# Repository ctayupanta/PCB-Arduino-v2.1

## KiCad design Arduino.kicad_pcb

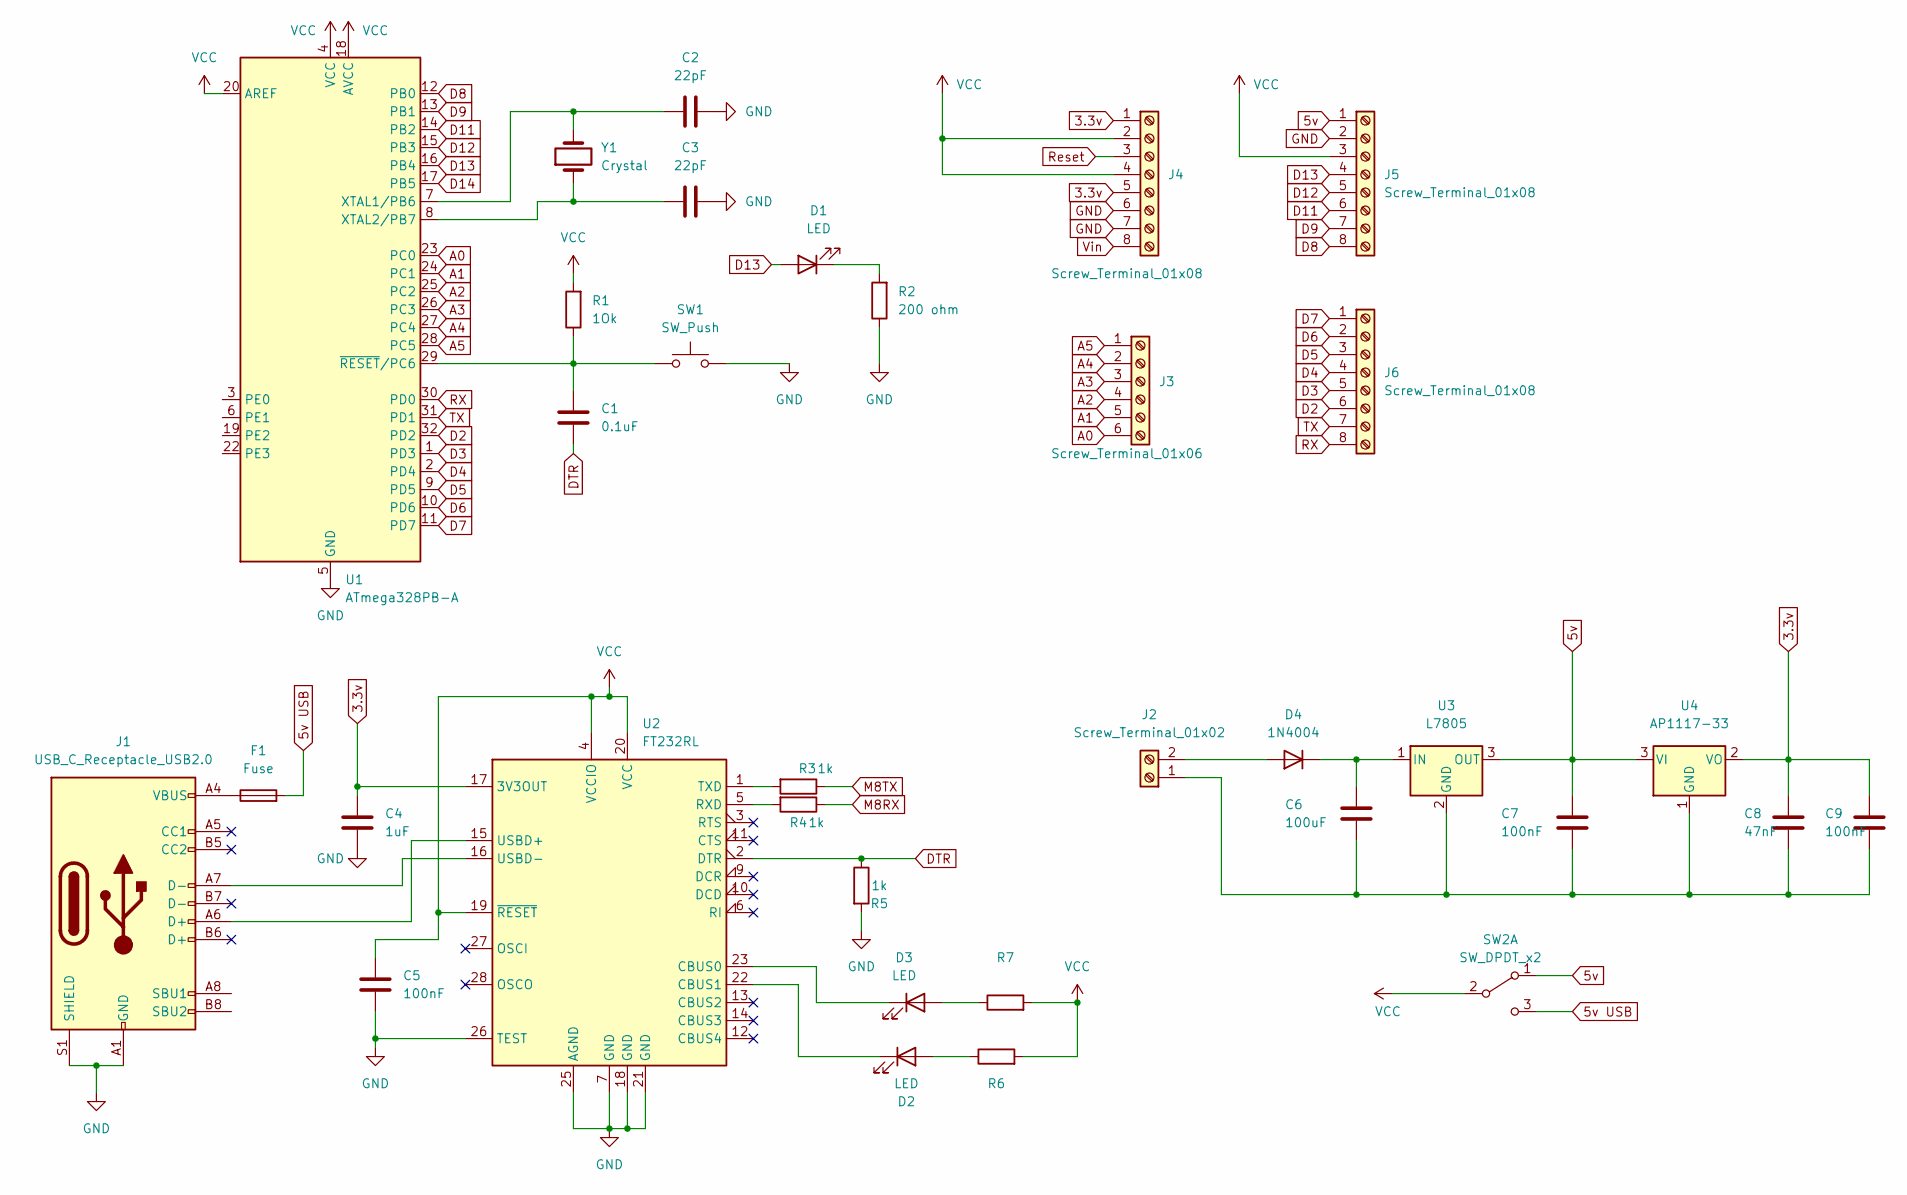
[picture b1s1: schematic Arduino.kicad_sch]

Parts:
C1: 0.1uF; C_0805_2012Metric
C2, C3: 22pF; C_0805_2012Metric
C4: 1uF; C_0805_2012Metric
C5, C7, C9: 100nF; C_0805_2012Metric
C6: 100uF; C_0805_2012Metric
C8: 47nF; C_0805_2012Metric
D1, D2, D3: LED; LED_0805_2012Metric
D4: 1N4004; D_0805_2012Metric
F1: Fuse; Fuse_1812_4532Metric
J1: USB_C_Receptacle_USB2.0; USB_C_Receptacle_HRO_TYPE-C-31-M-12
J2: Screw_Terminal_01x02; TerminalBlock_bornier-2_P5.08mm
J3: Screw_Terminal_01x06; PinSocket_1x06_P2.54mm_Vertical
J4, J5, J6: Screw_Terminal_01x08; PinSocket_1x08_P2.54mm_Vertical
R1: 1Ok; R_0805_2012Metric
R2: 200 ohm; R_0805_2012Metric
R3, R4, R5: 1k; R_0805_2012Metric
R6, R7: R_0805_2012Metric
SW1: SW_Push; SW_SPST_CK_KXT3
SW2: SW_DPDT_x2; SW_DIP_SPSTx01_Slide_6.7x4.1mm_W8.61mm_P2.54mm_LowProfile
U1: ATmega328PB-A; TQFP-32_7x7mm_P0.8mm
U2: FT232RL; SSOP-28_5.3x10.2mm_P0.65mm
U3: L7805; TO-252-2
U4: AP1117-33; SOT-223-3_TabPin2
Y1: Crystal; Crystal_SMD_0603-2Pin_6.0x3.5mm

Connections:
3.3v: C4.1, C8.1, C9.1, J4.1, J4.5, U2.17 (3V3OUT), U4.2 (VO)
5v: C7.1, J5.1, SW2.1 (A), U3.3 (OUT), U4.3 (VI)
5v USB: F1.2, SW2.3 (C)
A0: J3.6, U1.23 (PC0)
A1: J3.5, U1.24 (PC1)
A2: J3.4, U1.25 (PC2)
A3: J3.3, U1.26 (PC3)
A4: J3.2, U1.27 (PC4)
A5: J3.1, U1.28 (PC5)
D2: J6.6, U1.32 (PD2)
D3: J6.5, U1.1 (PD3)
D4: J6.4, U1.2 (PD4)
D5: J6.3, U1.9 (PD5)
D6: J6.2, U1.10 (PD6)
D7: J6.1, U1.11 (PD7)
D8: J5.8, U1.12 (PB0)
D9: J5.7, U1.13 (PB1)
D11: J5.6, U1.14 (PB2)
D12: J5.5, U1.15 (PB3)
D13: D1.2 (A), J5.4, U1.16 (PB4)
D14: U1.17 (PB5)
DTR: C1.2, R5.1, U2.2 (DTR)
GND: C2.2, C3.2, C4.2, C5.2, J1.A1 (GND), J1.A12 (GND), J1.B1 (GND), J1.B12 (GND), J1.S1 (SHIELD), J4.6, J4.7, J5.2, R2.1, R5.2, SW1.2, U1.5 (GND), U1.21 (GND), U2.7 (GND), U2.18 (GND), U2.21 (GND), U2.25 (AGND), U2.26 (TEST)
M8RX: R4.1
M8TX: R3.1
unnamed: C1.1, R1.1, SW1.1, U1.29 (~RESET/PC6)
unnamed: C2.1, U1.7 (XTAL1/PB6), Y1.2
unnamed: C3.1, U1.8 (XTAL2/PB7), Y1.1
unnamed: C6.1, D4.1 (K), U3.1 (IN)
unnamed: C6.2, C7.2, C8.2, C9.2, J2.1, U3.2 (GND), U4.1 (GND)
unnamed: D1.1 (K), R2.2
unnamed: D2.1 (K), U2.22 (CBUS1)
unnamed: D2.2 (A), R6.1
unnamed: D3.1 (K), U2.23 (CBUS0)
unnamed: D3.2 (A), R7.1
unnamed: D4.2 (A), J2.2
unnamed: F1.1, J1.A4 (VBUS), J1.A9 (VBUS), J1.B4 (VBUS), J1.B9 (VBUS)
unnamed: J1.A6 (D+), U2.15 (USBD+)
unnamed: J1.A7 (D-), U2.16 (USBD-)
unnamed: R3.2, U2.1 (TXD)
unnamed: R4.2, U2.5 (RXD)
RX: J6.8, U1.30 (PD0)
Reset: J4.3
TX: J6.7, U1.31 (PD1)
VCC: C5.1, J4.2, J4.4, J5.3, R1.2, R6.2, R7.2, SW2.2 (B), U1.4 (VCC), U1.18 (AVCC), U1.20 (AREF), U2.4 (VCCIO), U2.19 (~RESET), U2.20 (VCC)
Vin: J4.8

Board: 2 copper layers, 34 parts (0 on the bottom side), 40 nets, no tracks yet.

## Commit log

2022-09-06 Arduino v2.1
2022-09-06 Imagen Arduino
